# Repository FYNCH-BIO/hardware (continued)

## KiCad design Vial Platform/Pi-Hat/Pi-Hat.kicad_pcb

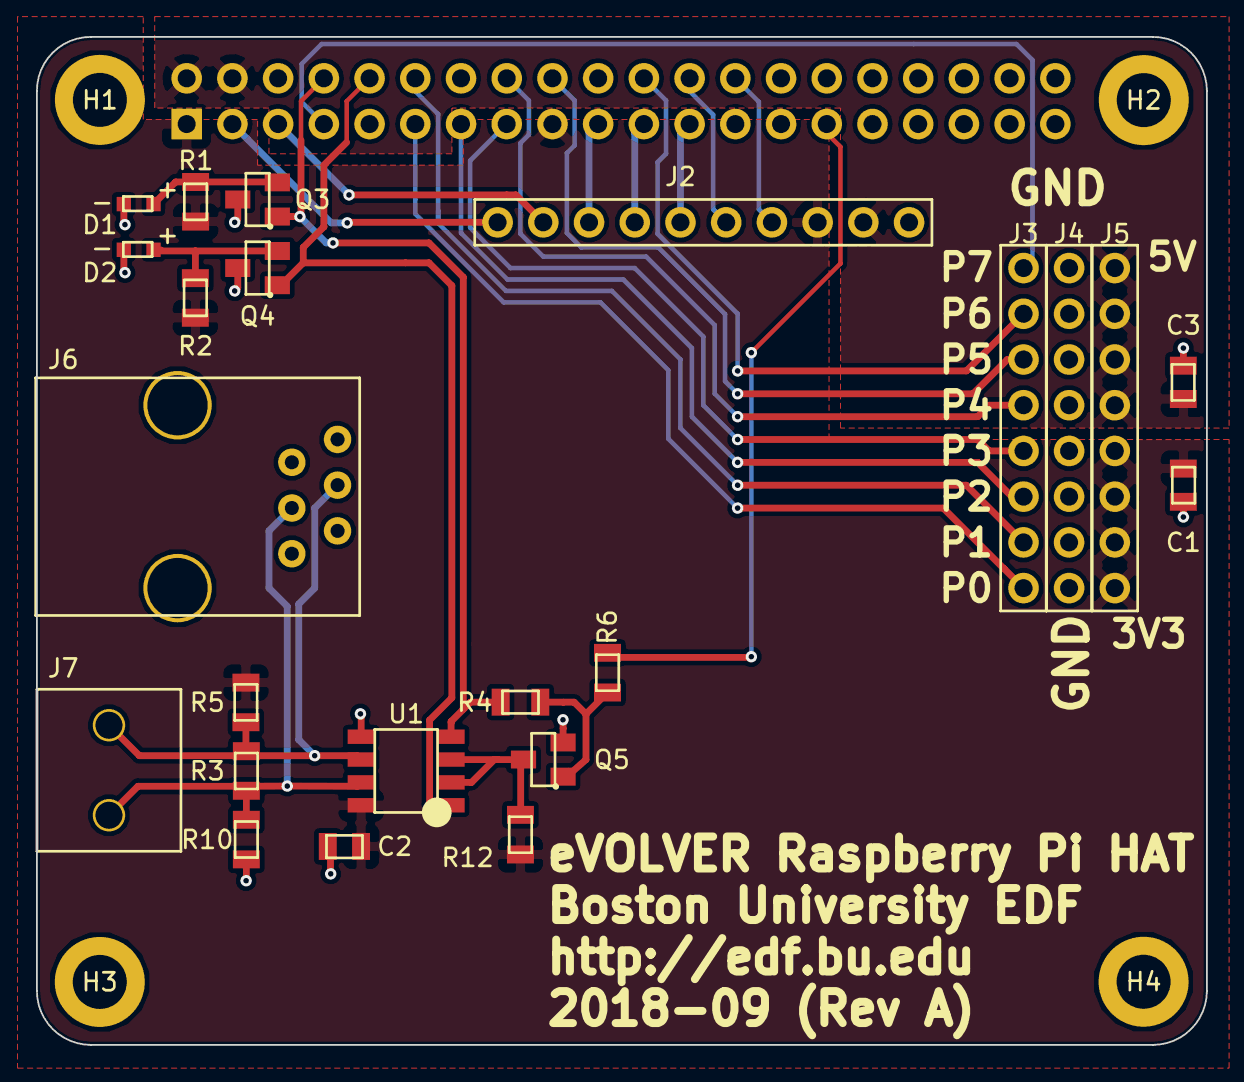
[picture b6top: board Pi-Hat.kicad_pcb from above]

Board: 2 copper layers, 65.0 x 56.0 mm, 28 parts (1 on the bottom side), 27 nets.

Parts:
C1, C2, C3: 1uF; C_0805_HS
D1, D2: LED; LED_0603
H1, H2, H3, H4: 3mm_Mounting_Hole; MH_plated
J1: raspberrypi_hat:OX40HAT; Connector_PinSocket_2.54mm
J2: Header_10Pin; 10Pin_Header
J3, J4, J5: Header_8Pin; 8Pin_Header
J6: RJ14; 609-5080-ND
J7: 2Screw_Term; 277-1667-ND
Q3, Q4: 2N7002
Q5: BSS123; 2N7002
R1, R2: 510; R_805_HS
R3, R6: DNP; R_805_HS
R4, R5, R10, R12: 10k; R_805_HS
U1: MAX481; SO-8

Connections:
/A: J6.3, J7.1, R3.1, R5.1, U1.6
/B: J6.4, J7.2, R3.2, R10.1, U1.7
/CE0: J1.24, J2.5
/CE1: J1.26, J2.4
/MISO: J1.21, J2.7
/MOSI: J1.19, J2.8
/P0: J1.11, J3.1
/P1: J1.12, J3.2
/P2: J1.13, J3.3
/P3: J1.15, J3.4
/P3V3: C1.1, C2.1, J1.1, J1.17, J2.3, J5.5, J5.6, J5.7, J5.8, R1.1, R2.1, R5.2, R12.2, U1.8
/P4: J1.16, J3.5
/P5: J1.18, J3.6
/P5V: C3.1, J1.2, J1.4, J2.2, J5.1, J5.2, J5.3, J5.4
/P6: J1.22, J3.7
/P7: J1.7, J3.8
/RXD: J1.10, Q4.1, U1.1
/SCL: J1.5, J2.9
/SCLK: J1.23, J2.6
/SDA: J1.3, J2.10
/TXD: J1.8, Q3.1, R4.1, U1.4
/TXD_2: J1.29, R6.1
GND: C1.2, C2.2, C3.2, D1.2, D2.2, J1.6, J1.9, J1.14, J1.20, J1.25, J1.30, J1.34, J1.39, J2.1, J4.1, J4.2, J4.3, J4.4, J4.5, J4.6, J4.7, J4.8, J6.2, J6.5, Q3.3, Q4.3, Q5.2, R10.2, U1.5
unnamed: D1.1, Q3.2, R1.2
unnamed: D2.1, Q4.2, R2.2
unnamed: Q5.1, R4.2, R6.2
unnamed: Q5.3, R12.1, U1.2, U1.3

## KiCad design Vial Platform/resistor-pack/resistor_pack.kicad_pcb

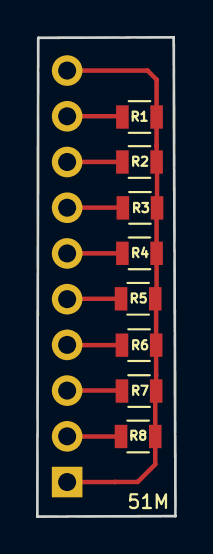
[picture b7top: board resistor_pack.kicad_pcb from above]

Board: 2 copper layers, 7.7 x 26.6 mm, 9 parts (1 on the bottom side), 9 nets.

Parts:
J1: Conn_01x10; Socket_Strip_Straight_1x10_Pitch2.54mm
R1, R2, R3, R4, R5, R6, R7, R8: R; R_0805

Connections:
unnamed: J1.1, J1.10, R1.2, R2.2, R3.2, R4.2, R5.2, R6.2, R7.2, R8.2
unnamed: J1.2, R8.1
unnamed: J1.3, R7.1
unnamed: J1.4, R6.1
unnamed: J1.5, R5.1
unnamed: J1.6, R4.1
unnamed: J1.7, R3.1
unnamed: J1.8, R2.1
unnamed: J1.9, R1.1

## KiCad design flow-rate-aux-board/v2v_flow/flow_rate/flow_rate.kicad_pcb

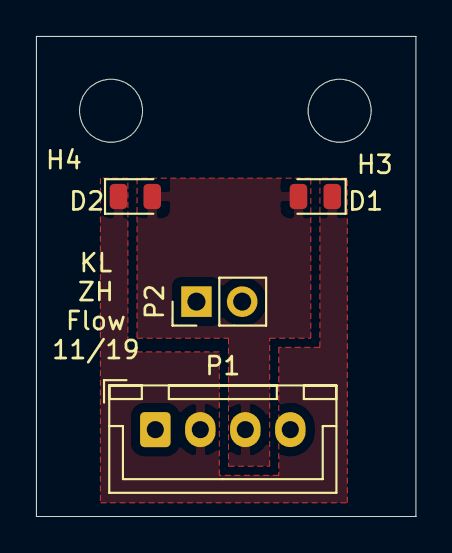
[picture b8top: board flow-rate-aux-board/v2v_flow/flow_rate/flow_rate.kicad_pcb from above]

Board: 2 copper layers, 21.1 x 26.7 mm, 6 parts (0 on the bottom side), 4 nets, no tracks yet.

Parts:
D1, D2: D; D_0805_2012Metric
H3, H4: MountingHole; MountingHole_3.5mm
P1: CONN_01X04; JST_XH_B4B-XH-A_1x04_P2.50mm_Vertical
P2: CONN_01X02; PinHeader_1x02_P2.54mm_Vertical

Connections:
/LED_GND: P1.4, P2.2
/LED_PWR: P1.1, P2.1
/OUT: D1.2, D2.2, P1.3
/V_SENSE: D1.1, D2.1, P1.2
